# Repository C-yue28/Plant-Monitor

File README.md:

<h1>Plant Monitor</h1> 

This smart, fully automated plant monitor system monitors soil moisture, atmospheric temperature/pressure, and humidity to determine when to water the plant, and then uses a small pump to water the plant. This is meant to be a project where I learn how to design a PCB, and it is also my first project with HackClub so I am getting used to this type of work. I kept it somewhat simple this time; if my custom devboard is successful I plan to build upon this project in the future and create an automated gardening system with a web dashboard.

The PCB in this project uses an RP2040 microcontroller. The power can either be supplied through USB connection or battery; when the USB is plugged in it charges the battery and takes priority in powering the RP2040 as well. The main external modules are: BME280 for temperature/humidity/pressure sensing, SSD1315 OLED display to display some basic information to user such as soil moisture/time till next watering, Maker Soil Moisture Sensor, 1S LiPo battery for power, and 4.5V DC water pump for a cheap way to water the plant. I also found some cheap tubing for the water pump as well. Below are pictures of the main PCB and the full assembly (with the small PCB for the BME280 as well). The tank for the water will be a separate plastic container; the DC motor is submersible (IP68) and so I can just directly place it in the water. 

How is this plant monitor more intelligent than others? Well, I decided to train a machine learning model on the gathered data so that it can predict the time until the next watering, which allows the user to know when to refill the water in the tank. To do this, I added time of day and then did some data augmenting. Specifically, I added some features to the data like moisture rate changes over the past 1, 3, and 6 hours to allow the model to understand how moisture is changing over time, and I also calculated the actual time until the next watering to allow for back propagation. The model's prediction is usually within +- XXX% of the actual time, which I believe is more than sufficient. External wiring is extremely minimal; the only thing which I hooked up was a button (on a breadboard) to pin 19 which connects to ground when pressed and toggles the OLED display. The BME280 breakout is also located on that same breadboard; OLED is secured to the gap in the front of the case and connected to the Grove connector; the soil moisture sensor is connected to the Grove connector and stuck into the soil; the DC motor is connected to the screw terminals and submersed in a separate plastic water tank. The battery is housed in the back corner of the case and connected into the JST 2P terminal. 

Bill of materials (the PCB-specific BOM can be found in the production folder)

| Name                 | Purpose                                                                                                        | Quantity | Total Cost (USD) | Link                                                                                                                                                                                                                                                                                    | Distributor  |
|----------------------|----------------------------------------------------------------------------------------------------------------|----------|------------------|-----------------------------------------------------------------------------------------------------------------------------------------------------------------------------------------------------------------------------------------------------------------------------------------|--------------|
| Grove Connectors     | JLCPCB is out of stock so I need to get these and solder them myself                                           | 1        | 0.99             | http://seeedstudio.com/Grove-Universal-4-pin-connector.html?srsltid=AfmBOorW7PKIxB2nBkeDA8cmDVeIM7P4xw2DvOuiTnTy1p6jJHWLyXrN                                                                                                                                                            | Seeed Studio |
| Grove Cables (5pc)   | Connect the modules which have the Grove connectors                                                            | 1        | 3.2              | https://www.seeedstudio.com/Grove-Universal-4-Pin-20cm-Unbuckled-Cable-5-PCs-Pack-p-749.html?srsltid=AfmBOoq_PWPlUHW6AhA9C06W1DHX0IDENz6RkAf7MmArpoaDusm0fHTv                                                                                                                           | Seeed Studio |
| PVC tubing           | Tubing for DC water pump to transport water to plant                                                           | 1        | 1.5              | https://www.adafruit.com/product/4545                                                                                                                                                                                                                                                   | Adafruit     |
| 0.96"" OLED Display  | To display information to user (soil humidity, time until next watering)                                       | 1        | 5.5              | https://www.electromaker.io/shop/product/grove-oled-yellowblue-display-096-ssd1315-spiiic-33v5v?gad_source=1&gad_campaignid=17338710367&gbraid=0AAAAAB8F3FmRMabQ0J10iEwfIvI6VSl6a&gclid=Cj0KCQjwkMjOBhC5ARIsADIdb3d52XNHvB0xUx85szcmNXmzkSiIRx9xRBb809RG0A6VtOCNXQ8NJkkaAqXOEALw_wcB    | Electromaker |
| LiPo battery         | To power the RP2040 so that I don't need to keep the USB plugged into something - modular design               | 1        | 7.95             | https://www.digikey.com/en/products/detail/adafruit-industries-llc/1578/5054539?gclsrc=aw.ds&gad_source=1&gad_campaignid=20243136172&gbraid=0AAAAADrbLlhvKmgdjMr2ASbfNgFbFfC-K&gclid=CjwKCAjwhLPOBhBiEiwA8_wJHHKKz7rCEnEKWuYEBjjljwh4XTezaZe1PkV-ABDO55FqAjQQXDC_LhoCzSYQAvD_BwE        | Digikey      |
| Soil Moisture Sensor | To sense soil moisture. Comes with the Grove cable                                                             | 1        | 6.5              | https://www.digikey.com/en/products/detail/seeed-technology-co-ltd/101020614/10451856?gclsrc=aw.ds&gad_source=1&gad_campaignid=20243136172&gbraid=0AAAAADrbLlg0W_J99eqvXgXNPPW8JPTJ3&gclid=Cj0KCQjwkMjOBhC5ARIsADIdb3eCSI7m6MAOEKuGfIUN2KJrR13pjfvRjO6_lb4Cy3DIPg3S2Vih_EMaAuvSEALw_wcB | Digikey      |
| 4.5V DC Water Pump   | To pump water so that the plants can be watered.                                                               | 1        | 3                | https://www.digikey.com/en/products/detail/pimoroni-ltd/COM3700/17095207?gclsrc=aw.ds&gad_source=1&gad_campaignid=20228387720&gbraid=0AAAAADrbLliRI0x7j5u_vN-RxMsu0GZb4&gclid=Cj0KCQjw77bPBhC_ARIsAGAjjV8Tcmb1D96uYqL9qOM_0nRBGDz4FpwRhH_SSa0cAxia4-QjcN9abrwaArgVEALw_wcB              | Digikey      |
| Main PCB             | Main devboard of the project                                                                                   | 1        | 54.81           | https://www.jlcpcb.com                                                                                                                                                                                                                                                                  | JLCPCB       |
| BME280               | Breakout is cheaper than PCB assembly so I decided to get a breakout of the BME280 for sensing rather than PCB | 1        | 15.99            | https://www.digikey.com/en/products/detail/sb-components-ltd/SKU27347/26694343                                                                                                                                                                                                          | Digikey      |
| 3D Printed Case      | To house the electronics                                                                                       | 1        | N/A              | N/A                                                                                                                                                                                                                                                                                     | Self-printed |

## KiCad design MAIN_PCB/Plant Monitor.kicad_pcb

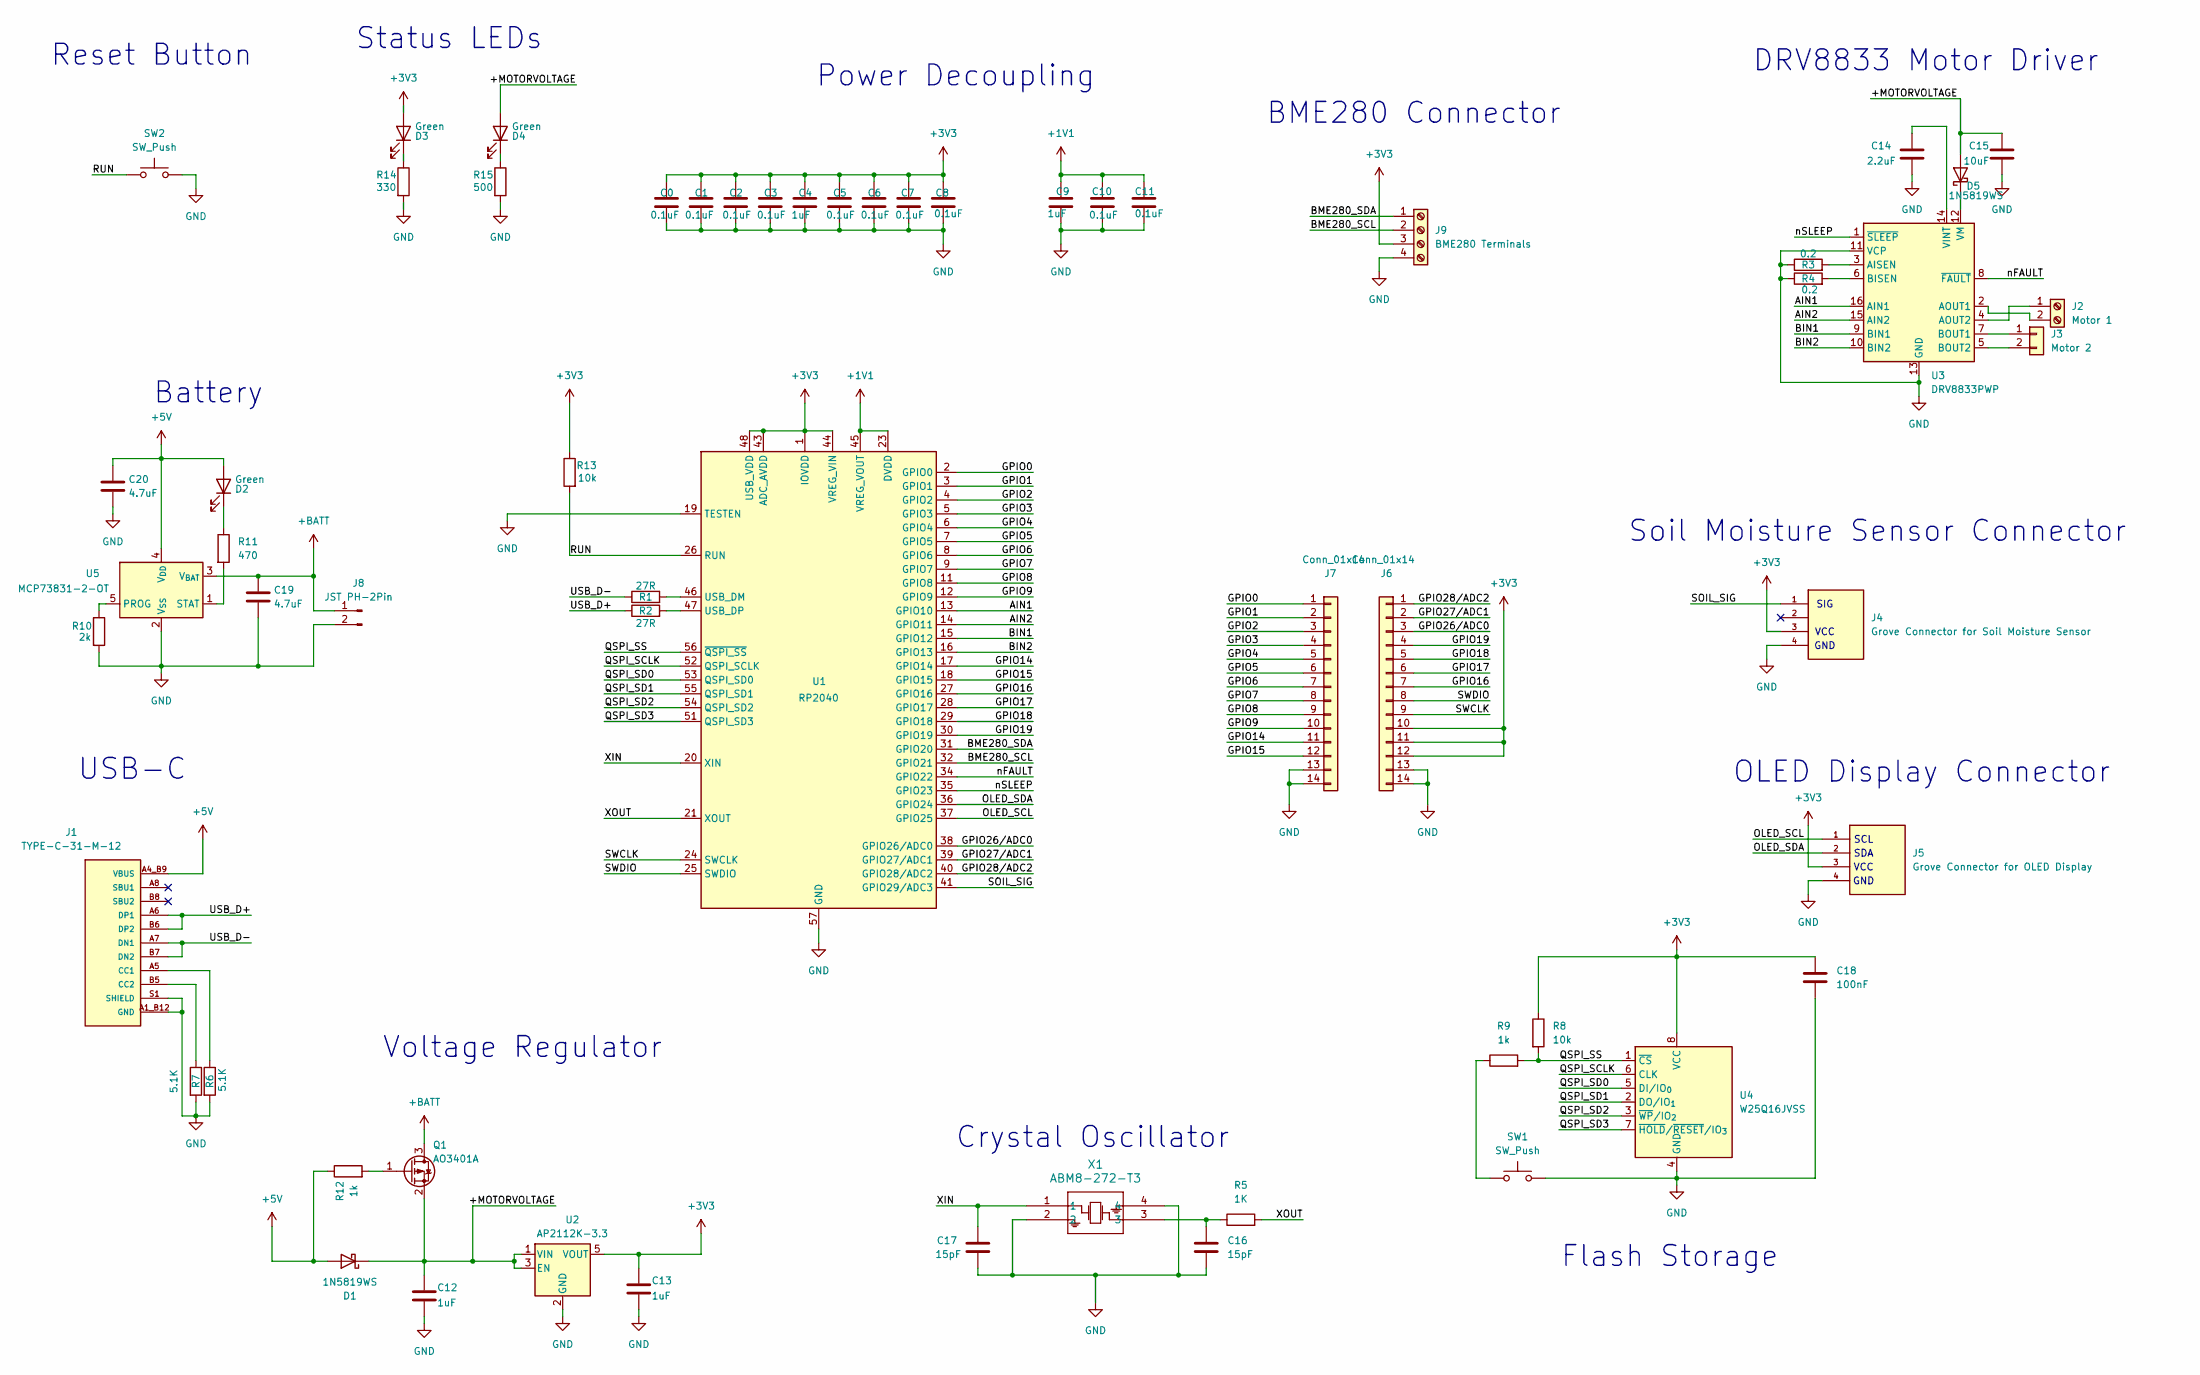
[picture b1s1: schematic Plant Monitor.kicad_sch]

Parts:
C0, C1, C2, C3, C5, C6, C7, C8, C10, C11: 0.1uF; C_0402_1005Metric
C4, C9, C12, C13: 1uF; C_0402_1005Metric
C14: 2.2uF; C_0603_1608Metric
C15: 10uF; C_0603_1608Metric
C16, C17: 15pF; C_0402_1005Metric
C18: 100nF; C_0402_1005Metric
C19, C20: 4.7uF; C_0603_1608Metric
D1, D5: 1N5819WS; D_SMA
D2, D3, D4: Green; LED_0603_1608Metric
J1: TYPE-C-31-M-12; HRO_TYPE-C-31-M-12; PARTREV 2020.12.08
J2: Motor 1; TerminalBlock_Phoenix_MKDS-1,5-2-5.08_1x02_P5.08mm_Horizont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
J3: Motor 2; PinHeader_1x02_P2.54mm_Vertical
J4: Grove Connector for Soil Moisture Sensor; SEEED_110990030; PARTREV A
J5: Grove Connector for OLED Display; SEEED_110990030; PARTREV A
J6, J7: Conn_01x14; PinHeader_1x14_P2.54mm_Vertical
J8: JST PH-2Pin; JST_PH_B2B-PH-K_1x02_P2.00mm_Vertical
J9: BME280 Terminals; TerminalBlock_Phoenix_MKDS-1,5-4_1x04_P5.00mm_Horizontal
Q1: AO3401A; SOT-23
R1, R2: 27R; R_0402_1005Metric
R3, R4: 0.2; R_0402_1005Metric
R5: 1K; R_0402_1005Metric
R6, R7: 5.1K; R_0402_1005Metric
R8, R13: 10k; R_0402_1005Metric
R9, R12: 1k; R_0402_1005Metric
R10: 2k; R_0402_1005Metric
R11: 470; R_0402_1005Metric
R14: 330; R_0402_1005Metric
R15: 500; R_0402_1005Metric
SW1, SW2: SW_Push; SW_Tactile_SPST_NO_Straight_CK_PTS636Sx25SMTRLFS
U1: RP2040; QFN-56-1EP_7x7mm_P0.4mm_EP3.2x3.2mm_ThermalVias
U2: AP2112K-3.3; SOT-23-5
U3: DRV8833PWP; HTSSOP-16-1EP_4.4x5mm_P0.65mm_EP3.4x5mm_Mask2.46x2.31mm_The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
U4: W25Q16JVSS; SOIC-8_5.3x5.3mm_P1.27mm
U5: MCP73831-2-OT; SOT-23-5
X1: ABM8-272-T3; ABM8-272-T3_ABR

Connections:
+1V1: C9.1, C10.1, C11.1, U1.23 (DVDD), U1.45 (VREG_VOUT), U1.50 (DVDD)
+3V3: C0.1, C1.1, C2.1, C3.1, C4.1, C5.1, C6.1, C7.1, C8.1, C13.1, C18.1, D3.2 (A), J4.3, J5.3, J6.10, J6.11, J6.12, J9.3, R8.1, R13.1, U1.1 (IOVDD), U1.10 (IOVDD), U1.22 (IOVDD), U1.33 (IOVDD), U1.42 (IOVDD), U1.43 (ADC_AVDD), U1.44 (VREG_VIN), U1.48 (USB_VDD), U1.49 (IOVDD), U2.5 (VOUT), U4.8 (VCC)
+5V: C20.1, D1.2 (A), D2.2 (A), J1.A4_B9 (VBUS), J1.B4_A9 (VBUS), R12.1, U5.4 (V_{DD})
+BATT: C19.1, J8.1, Q1.3 (D), U5.3 (V_{BAT})
/+MOTORVOLTAGE: C12.1, C15.1, D1.1 (K), D4.2 (A), D5.2 (A), Q1.2 (S), U2.1 (VIN), U2.3 (EN)
/AIN1: U1.13 (GPIO10), U3.16 (AIN1)
/AIN2: U1.14 (GPIO11), U3.15 (AIN2)
/BIN1: U1.15 (GPIO12), U3.9 (BIN1)
/BIN2: U1.16 (GPIO13), U3.10 (BIN2)
/BME280_SCL: J9.2, U1.32 (GPIO21)
/BME280_SDA: J9.1, U1.31 (GPIO20)
/GPIO0: J7.1, U1.2 (GPIO0)
/GPIO1: J7.2, U1.3 (GPIO1)
/GPIO2: J7.3, U1.4 (GPIO2)
/GPIO3: J7.4, U1.5 (GPIO3)
/GPIO4: J7.5, U1.6 (GPIO4)
/GPIO5: J7.6, U1.7 (GPIO5)
/GPIO6: J7.7, U1.8 (GPIO6)
/GPIO7: J7.8, U1.9 (GPIO7)
/GPIO8: J7.9, U1.11 (GPIO8)
/GPIO9: J7.10, U1.12 (GPIO9)
/GPIO14: J7.11, U1.17 (GPIO14)
/GPIO15: J7.12, U1.18 (GPIO15)
/GPIO16: J6.7, U1.27 (GPIO16)
/GPIO17: J6.6, U1.28 (GPIO17)
/GPIO18: J6.5, U1.29 (GPIO18)
/GPIO19: J6.4, U1.30 (GPIO19)
/GPIO26/ADC0: J6.3, U1.38 (GPIO26/ADC0)
/GPIO27/ADC1: J6.2, U1.39 (GPIO27/ADC1)
/GPIO28/ADC2: J6.1, U1.40 (GPIO28/ADC2)
/OLED_SCL: J5.1, U1.37 (GPIO25)
/OLED_SDA: J5.2, U1.36 (GPIO24)
/QSPI_SCLK: U1.52 (QSPI_SCLK), U4.6 (CLK)
/QSPI_SD0: U1.53 (QSPI_SD0), U4.5 (DI/IO_{0})
/QSPI_SD1: U1.55 (QSPI_SD1), U4.2 (DO/IO_{1})
/QSPI_SD2: U1.54 (QSPI_SD2), U4.3 (~WP/IO_{2})
/QSPI_SD3: U1.51 (QSPI_SD3), U4.7 (~HOLD/~RESET/IO_{3})
/QSPI_SS: R8.2, R9.2, U1.56 (~QSPI_SS), U4.1 (~CS)
/RUN: R13.2, SW2.1, SW2.3, U1.26 (RUN)
/SOIL_SIG: J4.1, U1.41 (GPIO29/ADC3)
/SWCLK: J6.9, U1.24 (SWCLK)
/SWDIO: J6.8, U1.25 (SWDIO)
/USB_D+: J1.A6 (DP1), J1.B6 (DP2), R2.1
/USB_D-: J1.A7 (DN1), J1.B7 (DN2), R1.1
/XIN: C17.1, U1.20 (XIN), X1.1
/XOUT: R5.2, U1.21 (XOUT)
/nFAULT: U1.34 (GPIO22), U3.8 (~FAULT)
/nSLEEP: U1.35 (GPIO23), U3.1 (~SLEEP)
GND: C0.2, C1.2, C2.2, C3.2, C4.2, C5.2, C6.2, C7.2, C8.2, C9.2, C10.2, C11.2, C12.2, C13.2, C14.2, C15.2, C16.2, C17.2, C18.2, C19.2, C20.2, J1.A1_B12 (GND), J1.B1_A12 (GND), J1.S1 (SHIELD), J1.S2 (SHIELD), J1.S3 (SHIELD), J1.S4 (SHIELD), J4.4, J5.4, J6.13, J6.14, J7.13, J7.14, J8.2, J9.4, R3.1, R4.1, R6.2, R7.2, R10.2, R14.2, R15.2, SW1.2, SW1.4, SW2.2, SW2.4, U1.19 (TESTEN), U1.57 (GND), U2.2 (GND), U3.11 (VCP), U3.13 (GND), U3.17 (GND), U4.4 (GND), U5.2 (V_{SS}), X1.2, X1.4
unnamed: C16.1, R5.1, X1.3
unnamed: D2.1 (K), R11.1
unnamed: D3.1 (K), R14.1
unnamed: D4.1 (K), R15.1
unnamed: D5.1 (K), U3.12 (VM)
unnamed: J1.A5 (CC1), R6.1
unnamed: J1.B5 (CC2), R7.1
unnamed: J2.1, U3.4 (AOUT2)
unnamed: J2.2, U3.2 (AOUT1)
unnamed: J3.1, U3.7 (BOUT1)
unnamed: J3.2, U3.5 (BOUT2)
unnamed: Q1.1 (G), R12.2
unnamed: R9.1, SW1.1, SW1.3
unnamed: R1.2, U1.46 (USB_DM)
unnamed: R2.2, U1.47 (USB_DP)
unnamed: R3.2, U3.3 (AISEN)
unnamed: R4.2, U3.6 (BISEN)
unnamed: C14.1, U3.14 (VINT)
unnamed: R10.1, U5.5 (PROG)
unnamed: R11.2, U5.1 (STAT)

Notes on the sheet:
SDA
GND
Reset Button
DRV8833 Motor Driver
Power Decoupling
VCC
USB-C
Voltage Regulator
SIG
SCL
Battery
Flash Storage
Crystal Oscillator
Status LEDs
OLED Display Connector
Soil Moisture Sensor Connector
BME280 Connector

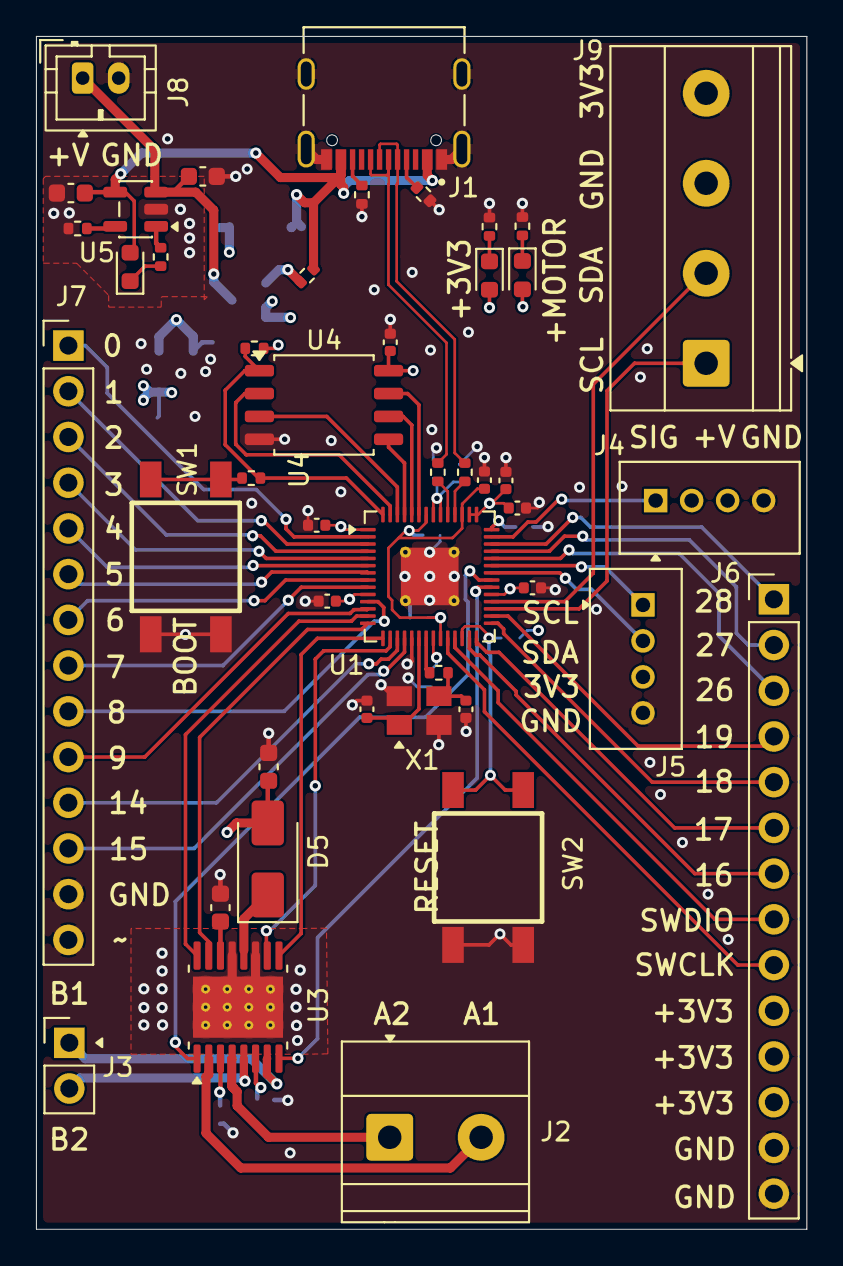
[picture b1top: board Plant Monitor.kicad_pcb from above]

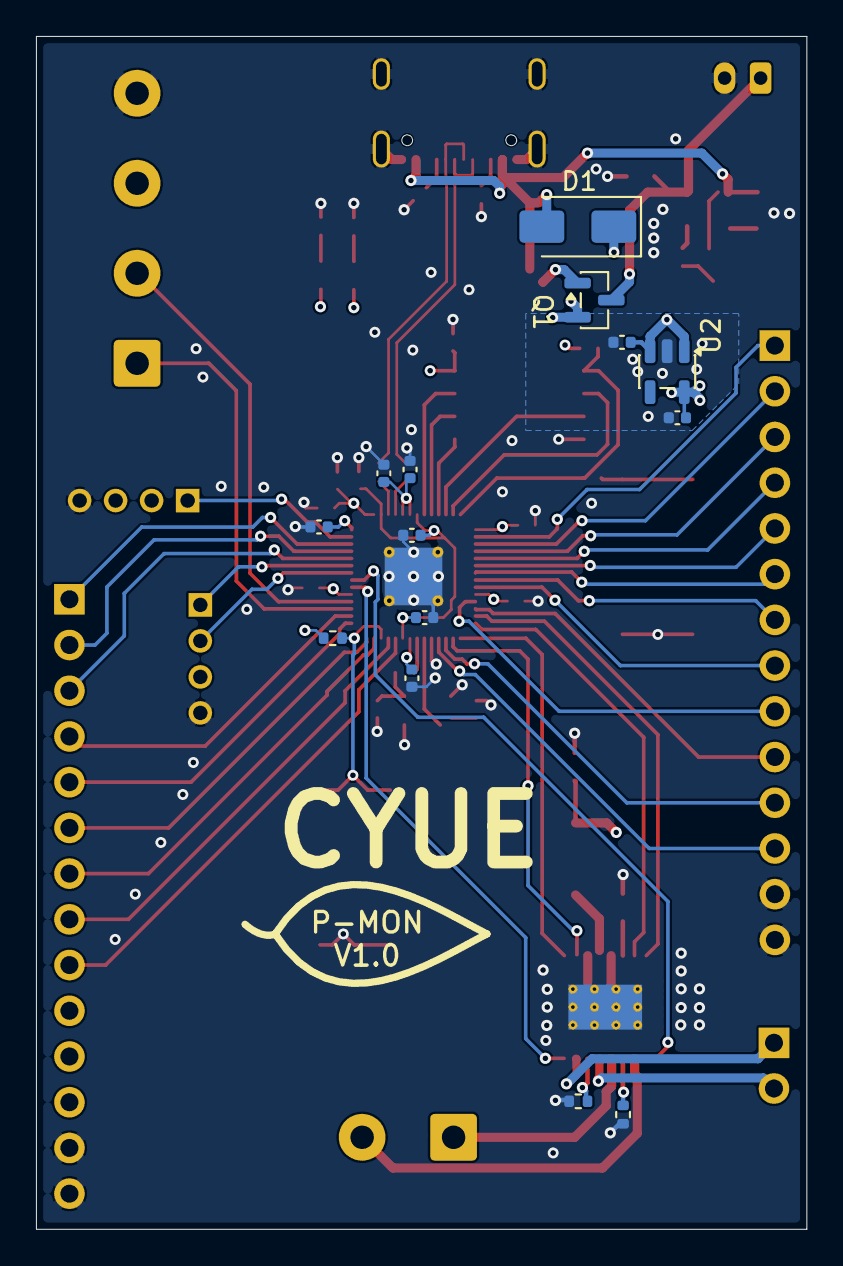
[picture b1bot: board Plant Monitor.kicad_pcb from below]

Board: 6 copper layers, 42.8 x 66.3 mm, 59 parts (14 on the bottom side), 69 nets.

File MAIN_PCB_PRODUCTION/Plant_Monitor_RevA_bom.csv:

Designator,Footprint,Quantity,Value,LCSC Part #
"C0, C1, C10, C11, C2, C3, C5, C6, C7, C8",0402,10,0.1uF,
"C12, C13, C4, C9",0402,4,1uF,
C14,0603,1,2.2uF,
C15,0603,1,10uF,
"C16, C17",0402,2,15pF,
C18,0402,1,100nF,
"C19, C20",0603,2,4.7uF,
"D1, D5",D_SMA,2,1N5819WS,
"D2, D3, D4",0603,3,Green,
J1,HRO_TYPE-C-31-M-12,1,TYPE-C-31-M-12,
J2,"TerminalBlock_Phoenix_MKDS-1,5-2-5.08_1x02_P5.08mm_Horizontal",1,Motor 1,
J3,PinHeader_1x02_P2.54mm_Vertical,1,Motor 2,
J4,SEEED_110990030,1,Grove Connector for Soil Moisture Sensor,
J5,SEEED_110990030,1,Grove Connector for OLED Display,
"J6, J7",PinHeader_1x14_P2.54mm_Vertical,2,Conn_01x14,
J8,JST_PH_B2B-PH-K_1x02_P2.00mm_Vertical,1,JST PH-2Pin,
J9,"TerminalBlock_Phoenix_MKDS-1,5-4_1x04_P5.00mm_Horizontal",1,BME280 Terminals,
Q1,SOT-23,1,AO3401A,
"R1, R2",0402,2,27R,
R10,0402,1,2k,
R11,0402,1,470,
"R12, R5, R9",0402,3,1k,
"R13, R8",0402,2,10k,
R14,0402,1,330,
R15,0402,1,500,
"R3, R4",0402,2,0.2,
"R6, R7",0402,2,5.1K,
"SW1, SW2",SW_Tactile_SPST_NO_Straight_CK_PTS636Sx25SMTRLFS,2,SW_Push,
U1,QFN-56-1EP_7x7mm_P0.4mm_EP3.2x3.2mm_ThermalVias,1,RP2040,
U2,SOT-23-5,1,AP2112K-3.3,
U3,HTSSOP-16-1EP_4.4x5mm_P0.65mm_EP3.4x5mm_Mask2.46x2.31mm_ThermalVias,1,DRV8833PWP,
U4,Winbond_USON-8-1EP_3x2mm_P0.5mm_EP0.2x1.6mm,1,W25Q16JVSS,
U5,SOT-23-5,1,MCP73831-2-OT,
X1,ABM8-272-T3_ABR,1,ABM8-272-T3,

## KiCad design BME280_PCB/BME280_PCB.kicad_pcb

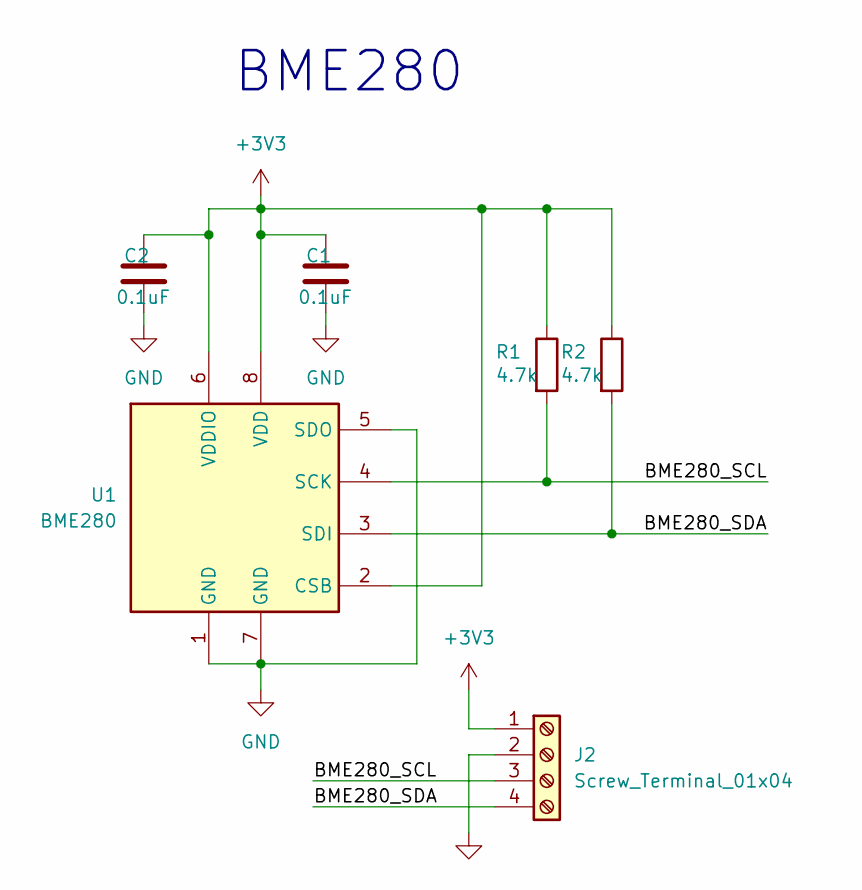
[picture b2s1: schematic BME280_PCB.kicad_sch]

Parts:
C1, C2: 0.1uF; C_0402_1005Metric
J2: Screw_Terminal_01x04; TerminalBlock_Phoenix_MKDS-1,5-4_1x04_P5.00mm_Horizontal
R1, R2: 4.7k; R_0402_1005Metric
U1: BME280; Bosch_LGA-8_2.5x2.5mm_P0.65mm_ClockwisePinNumbering

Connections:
+3V3: C1.1, C2.1, J2.1, R1.1, R2.1, U1.2 (CSB), U1.6 (VDDIO), U1.8 (VDD)
/BME280_SCL: J2.3, R1.2, U1.4 (SCK)
/BME280_SDA: J2.4, R2.2, U1.3 (SDI)
GND: C1.2, C2.2, J2.2, U1.1 (GND), U1.5 (SDO), U1.7 (GND)

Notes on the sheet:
BME280

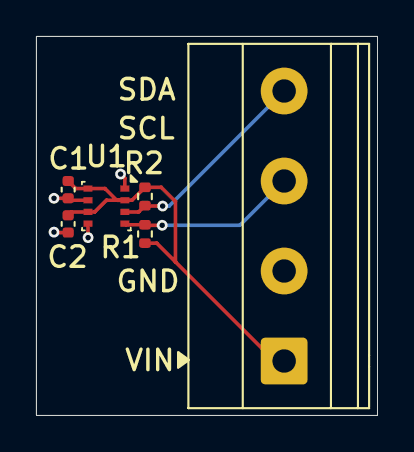
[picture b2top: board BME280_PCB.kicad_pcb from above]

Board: 2 copper layers, 18.9 x 21.1 mm, 6 parts (0 on the bottom side), 4 nets.

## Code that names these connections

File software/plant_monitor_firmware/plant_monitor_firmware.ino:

/*

Firmware for Plant Monitor HackClub Stasis Project

*/

#include <Wire.h>
#include <Adafruit_Sensor.h>
#include <Adafruit_BME280.h>
#include <U8x8lib.h>

// mode: normal (0) or data collection (1) (sample more often to gather data for ML model)

const int MODE = 0;
const double K;
const double a;
const double b;
const double c;

//GPIO pins:

const int AIN1 = 10;
const int AIN2 = 11;
const int SLEEP = 23;

const int BME280_SDA = 20;
const int BME280_SCL = 21;

const int OLED_SDA = 24;
const int OLED_SCL = 25;

const int SOIL_SIG = 29;

const int BUTTON = 19;

// data readings

double soil_moisture = 0;
double SOIL_MOISTURE_THRESHOLD = 0.40; // arbitrary value found online (40%)
const double M_param = pow(SOIL_MOISTURE_THRESHOLD, 1-a);

Adafruit_BME280 bme280;
double temperature;
double humidity;
double pressure;

U8X8_SSD1315_128X64_NONAME_HW_I2C oled(U8X8_PIN_NONE, OLED_SCL, OLED_SDA);
bool OLED_ON = 0;
int OLED_ON_MILLIS = 0;

// time
int timeStep = 1800000; // ms; 30 minutes

struct days_hours {
  int days;
  int hours;
}

void readData() {

  // sample each sensor multiple times; take an average
  sum_moisture = 0;
  sum_temp = 0;
  sum_hum = 0;
  sum_pressure = 0;

  for (int i = 0; i < SAMPLE_COUNT; i++) {

    // for now, I cannot know what values this will get - it is a relative measurement; as moisture goes up analog voltage goes down 
    sum_moisture += analogRead(SOIL_SIG) / 3.3; // for now I will simply take it as a percentage of its max; I will definitely have to adjust this

    sum_temp += bme280.readTemperature();
    sum_hum += bme280.readHumidity();
    sum_pressure += bme280.readPressure() / 1000.0F;

  }

  soil_moisture = sum_moisture / SAMPLE_COUNT;
  temperature = sum_temp / SAMPLE_COUNT;
  humidity = sum_hum / SAMPLE_COUNT;
  pressure = sum_pressure / SAMPLE_COUNT;

}

days_hours predictTime() {
  // integrated the rate calculation function using the assumption that (1+b*T)(1-c*H) would remain relatively constant enough for me to treat it as such
  // this was done with the help of many online sources and ChatGPT
  time_until_next_water = (M_param-pow(soil_moisture, 1-a)) / (k*(1+b*temperature)*(1-c*humidity)*(1-a))
}

void toggleDisplay() {

  if (OLED_ON) {
    OLED_ON = false;
    oled.clearDisplay();
    return;
  }

  time_until_next_water = predictTime();

  oled.drawString(0, 0, "Moisture: %.2f", soil_moisture);
  oled.drawString(0, 1, "Temp(C): %.2f", temperature);
  oled.drawString(0, 2, "Humidity: %.2f%%", humidity);
  oled.drawString(0, 3, "Pressure: %.1f atm", pressure/760.0F);
  if (!MODE) {
    oled.drawString(0, 4, "Time until next")
    oled.drawString(0, 5, "water: %d:%d", time_until_next_water.days, time_until_next_water.hours);
  }

  OLED_ON = true;
  delay(50); // debounce button

}

void outputData(bool hasWatered) {
  Serial.println("SOIL: %f", soil_moisture);
  Serial.println("TEMPERATURE: %f", temperature);
  Serial.println("HUMIDITY: %f", humidity);
  Serial.println("WATERED: %d", hasWatered ? 1 : 0);
  Serial.println("MILLIS: %f", millis()); // for calculating evaporation rate
}

void waterPlant() {
  analogWrite(AIN1, MOTOR_SPEED);
  delay(5000);
  analogWrite(AIN1, 0);
}

void setup() {

  // initialize I2C buses
  Wire.setSDA(BME280_SDA);
  Wire.setSCL(BME280_SCL);

  // Wire1.setSDA(OLED_SDA);
  // Wire1.setSCL(OLED_SCL);
  
  oled.begin();
  bme280.begin(0x76, &Wire);
  Serial.begin(115200);

  // pin modes
  pinMode(AIN1, OUTPUT);
  pinMode(AIN2, OUTPUT);
  pinMode(SLEEP, OUTPUT);
  pinMode(SOIL_SIG, INPUT);
  pinMode(BUTTON, INPUT_PULLUP);

  attachInterrupt(digitalPinToInterrupt(BUTTON), toggleDisplay, LOW);
  digitalWrite(SLEEP, HIGH);

  oled.setFont(u8x8_font_8x13_1x2_f);
  if (MODE) {
    timeStep /= 6; // 30 minutes down to 5 minutes
  }

  Serial.println("Ready.");  

}

void loop() {

  readData();

  if (soil_moisture < SOIL_MOISTURE_THRESHOLD) {
    waterPlant();
    outputData(true);
  } else {
    outputData(false);
  }

  delay(timeStep);

}

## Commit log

2026-03-31 First commit with git
2026-03-31 Commit all project files as of right now
2026-03-31 Restarting
2026-03-31 Add gitignore
2026-03-31 Restarting again, figured the issue out finally
2026-03-31 Add .gitignore
2026-03-31 First actual commit with git
2026-04-02 Re-commit .gitignore with new schematic included
2026-04-02 Finished main PCB schematic, as well as BMP280 schematic
2026-04-05 Updated PCB design+schematic
2026-04-11 Finished main PCB
2026-04-12 Finished all PCBs, initial CAD complete
2026-04-22 Added new item to gitignore
2026-04-22 Added CAD, production files for main PCB
2026-04-24 Wrote firmware for the RP2040 and began working on the implementation of the ML model
2026-04-26 Finished first draft of firmware, including ML model
2026-04-26 Add images to README
2026-04-27 Finished README, added full BOM, deleted the unnecessary BME280 PCB files
2026-04-27 Finalize README for submission
2026-06-13 Revision D of PCB design
2026-06-13 Updated BOM and production details
2026-06-16 Added media
2026-06-17 Added wiring/schematic
2026-06-28 Rearrange media
2026-06-28 Add pcb design image
